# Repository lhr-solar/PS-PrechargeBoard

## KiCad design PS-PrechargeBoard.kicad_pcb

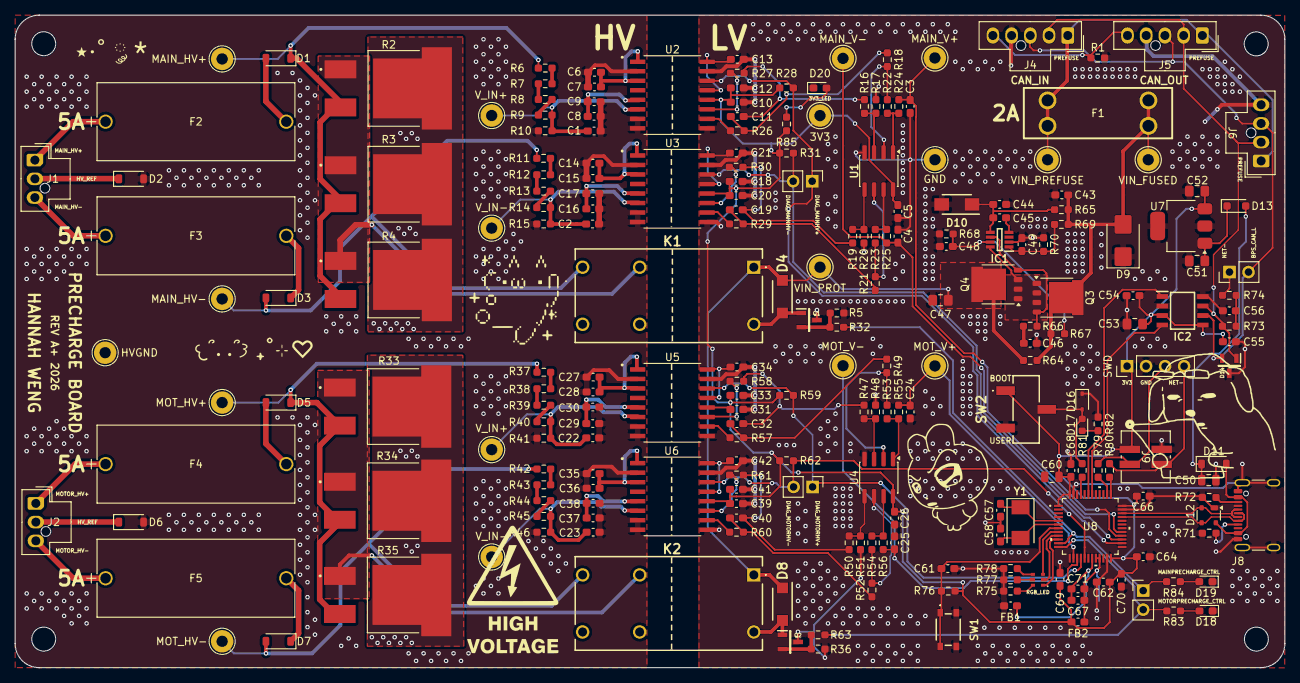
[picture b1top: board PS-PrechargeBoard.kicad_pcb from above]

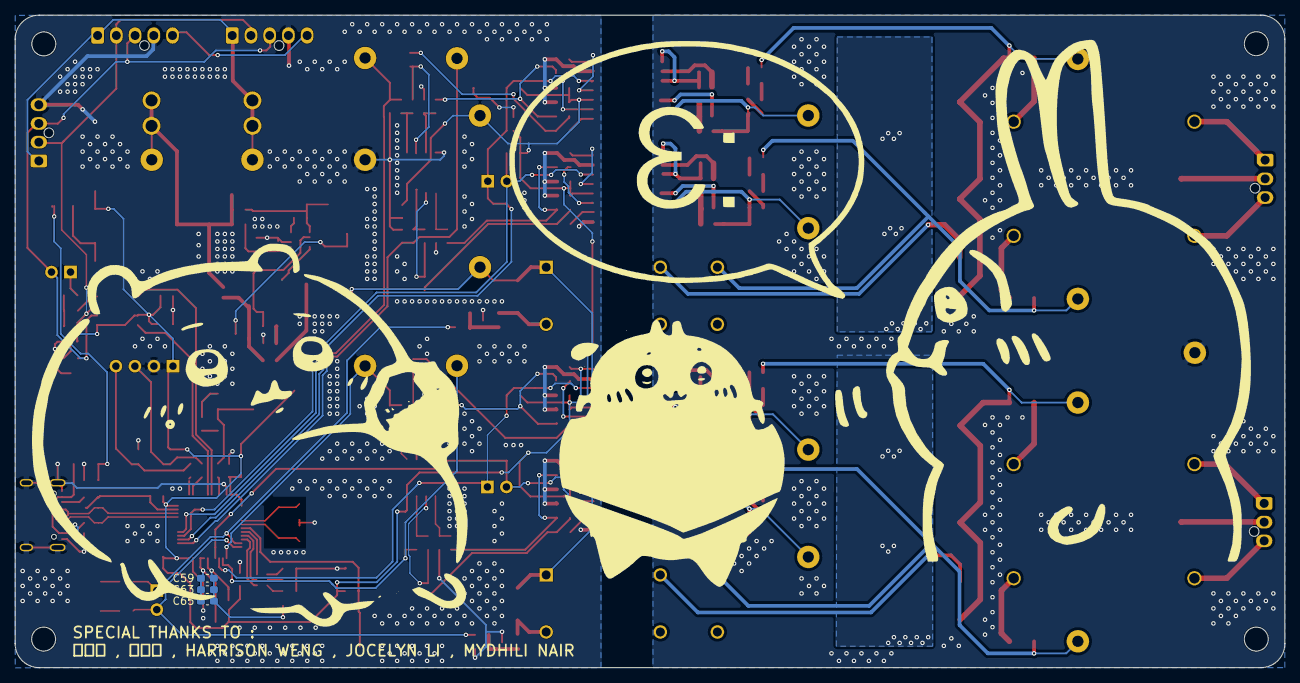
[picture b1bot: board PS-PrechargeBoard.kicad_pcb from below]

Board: 2 copper layers, 169.5 x 87.1 mm, 236 parts (3 on the bottom side), 136 nets.

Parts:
C1, C2, C5, C10, C18, C22, C23, C26, C31, C39, C44, C65, C67: 1u; C_0603_1608Metric_Pad1.08x0.95mm_HandSolder
C3, C4, C11, C19, C24, C25, C32, C40, C46: 10n; C_0603_1608Metric_Pad1.08x0.95mm_HandSolder
C6, C9, C12, C14, C17, C20, C27, C30, C33, C35, C38, C41: 1n; C_0603_1608Metric_Pad1.08x0.95mm_HandSolder
C7, C8, C13, C15, C16, C21, C28, C29, C34, C36, C37, C42, C71: 100n; C_0603_1608Metric_Pad1.08x0.95mm_HandSolder
C43, C48, C49, C54, C55, C56, C59, C61, C62, C63, C64, C66, C68, C69, C70: 0.1u; C_0603_1608Metric_Pad1.08x0.95mm_HandSolder
C45: 220n; C_0603_1608Metric_Pad1.08x0.95mm_HandSolder
C47, C51, C52, C53: 10u; C_0805_2012Metric_Pad1.18x1.45mm_HandSolder
C50, C60: 10u; C_0805_2012Metric
C57, C58: 26p; C_0603_1608Metric_Pad1.08x0.95mm_HandSolder
D1, D2, D3, D5, D6, D7: RSX068MP2STR; D_SOD-123
D4, D8: VSSAF510HM3/H; SODFL5226X100N
D9: SMBJ15CA; D_SMB
D10: SMAF4758A; SODFL5026X125N
D11: D_Schottky; D_SOD-123
D12: SP0503BAHT; SOT-143
D13: SBA130CH-AU_R1_000A1; D_SOD-323_HandSoldering
D14: CDSOT23-T24CAN
D15: RGB_LED
D16: TVS; D_SOD-323
D17: LED; LED_0603_1608Metric
D18, D19, D20: LED; LED_0603_1608Metric_Pad1.05x0.95mm_HandSolder
F1: 2A; Fuse-3557-2
F2, F3, F4, F5: 5A; HV-Fuse
FB1, FB2: FerriteBead; C_0603_1608Metric_Pad1.08x0.95mm_HandSolder
H1, H2, H3, H4: MountingHole; MountingHole_3.2mm_M3
IC1: LM74502DDFR
IC2: TCAN3413DR
J1: HV_Main; Molex_Nano-Fit_105309-xx03_1x03_P2.50mm_Vertical
J2: HV_Motor; Molex_Nano-Fit_105309-xx03_1x03_P2.50mm_Vertical
J3: MOTOR_DIAG; PinHeader_1x02_P2.54mm_Vertical
J4: CAN_IN; Molex_Nano-Fit_105309-xx05_1x05_P2.50mm_Vertical
J5: CAN_OUT; Molex_Nano-Fit_105309-xx05_1x05_P2.50mm_Vertical
J6: DEBUG_NANO; Molex_Nano-Fit_105309-xx04_1x04_P2.50mm_Vertical
J7: PRECHARGE_CTRL; PinHeader_1x02_P2.54mm_Vertical
J8: USB_C_Receptacle_USB2.0_16P; USB_C_Receptacle_GCT_USB4105-xx-A_16P_TopMnt_Horizontal
J9: SWD_Header; SWD_Conn
J10: SWD; PinHeader_1x04_P2.54mm_Vertical
J11: MAIN_DIAG; PinHeader_1x02_P2.54mm_Vertical
JP1: TRM; PinHeader_1x02_P2.54mm_Vertical
K1, K2: DE1a-12V; DE1a12V
Q1, Q2: NMOS; SOT95P237X112-3N
Q3, Q4: PSMN012-100YS; LFPAK56
R1, R64: 0; R_0603_1608Metric_Pad0.98x0.95mm_HandSolder
R2, R3, R4, R33, R34, R35: 50; RES_PWR263S-35-3300F
R5, R10, R15, R16, R17, R18, R19, R20, R21, R22, R23, R36, R41, R46, R47, R48, R49, R50, R51, R52, R53, R54, R65, R76, R81: 10k; R_0603_1608Metric_Pad0.98x0.95mm_HandSolder
R6, R7, R8, R9, R11, R12, R13, R14, R37, R38, R39, R40, R42, R43, R44, R45: 180k; R_0603_1608Metric_Pad0.98x0.95mm_HandSolder
R24, R25, R26, R27, R29, R30, R55, R56, R57, R58, R60, R61: 10; R_0603_1608Metric_Pad0.98x0.95mm_HandSolder
R28, R31, R59, R62: 47k; R_0603_1608Metric_Pad0.98x0.95mm_HandSolder
R32, R63: 100; R_0603_1608Metric_Pad0.98x0.95mm_HandSolder
R66: 33; R_0603_1608Metric_Pad0.98x0.95mm_HandSolder
R67, R69: 100k; R_0603_1608Metric_Pad0.98x0.95mm_HandSolder
R68: 7.32k; R_0603_1608Metric_Pad0.98x0.95mm_HandSolder
R70: 15.8k; R_0603_1608Metric_Pad0.98x0.95mm_HandSolder
R71, R72: 5.1k; R_0603_1608Metric_Pad0.98x0.95mm_HandSolder
R73, R74: 60; R_0603_1608Metric_Pad0.98x0.95mm_HandSolder
R75, R77, R78, R82, R83, R84, R85: 1k; R_0603_1608Metric_Pad0.98x0.95mm_HandSolder
R79, R80: 22; R_0603_1608Metric_Pad0.98x0.95mm_HandSolder
SW1: Reset; TL3365AF180QG
SW2: SW_SPDT; BootSW
TP1: MOT_HV+; TestPoint_THTPad_D3.0mm_Drill1.5mm
TP2: MAIN_HV+; TestPoint_THTPad_D3.0mm_Drill1.5mm
TP3: HVGND; TestPoint_THTPad_D3.0mm_Drill1.5mm
TP4: MAIN_HV-; TestPoint_THTPad_D3.0mm_Drill1.5mm
TP5: MOT_HV-; TestPoint_THTPad_D3.0mm_Drill1.5mm
TP6: 3V3; TestPoint_THTPad_D3.0mm_Drill1.5mm
TP7: VIN_PROT; TestPoint_THTPad_D3.0mm_Drill1.5mm
TP8: VIN_PREFUSE; TestPoint_THTPad_D3.0mm_Drill1.5mm
TP9: MAIN_V+; TestPoint_THTPad_D3.0mm_Drill1.5mm
TP10: MAIN_V-; TestPoint_THTPad_D3.0mm_Drill1.5mm
TP11: GND; TestPoint_THTPad_D3.0mm_Drill1.5mm
TP12: VIN_FUSED; TestPoint_THTPad_D3.0mm_Drill1.5mm
TP13: MOT_V+; TestPoint_THTPad_D3.0mm_Drill1.5mm
TP14: MOT_V-; TestPoint_THTPad_D3.0mm_Drill1.5mm
TP15, TP19: V_IN+; TestPoint_THTPad_D3.0mm_Drill1.5mm
TP16, TP20: V_IN-; TestPoint_THTPad_D3.0mm_Drill1.5mm
U1, U4: TLV9002QDRQ1; SOIC-8_3.9x4.9mm_P1.27mm
U2, U3, U5, U6: SOIC127P1030X265-16N
U7: MCP1826S; SOT-223-3_TabPin2
U8: STM32G473CETx; 48PinMCU
Y1: Crystal; Crystal_SMD_Abracon_ABM3-2Pin_5.0x3.2mm

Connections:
3V3: C5.1, C10.1, C12.1, C18.1, C20.1, C26.1, C31.1, C33.1, C39.1, C41.1, C52.2, C53.1, C54.1, C55.1, C60.1, C62.1, C64.1, C66.1, C68.1, C69.1, C70.1, FB2.1, IC2.3 (VCC), IC2.5 (SHDNV_IO), J9.1, J10.1, R28.1, R31.1, R59.1, R62.1, R76.2, R85.1, SW2.1 (A), TP6.1 (1_1), U1.8 (V+), U2.12 (VDD), U3.12 (VDD), U4.8 (V+), U5.12 (VDD), U6.12 (VDD), U7.3 (VO), U8.1 (VBAT), U8.24 (VDD), U8.36 (VDD), U8.48 (VDD)
/48PinMCU/BOOT0: R81.1, U8.45 (PB8-BOOT0)
/48PinMCU/GNDA: C59.2, C63.2, C65.2, C67.2, C71.2, FB1.1, U8.19 (VSSA)
/48PinMCU/NRST: C61.1, R76.1, SW1.1, U8.7 (PG10-NRST)
/48PinMCU/PA0: D15.5, U8.8 (PA0-GPIO_BLUE)
/48PinMCU/PA1: D15.3, U8.9 (PA1_GPIO_RED)
/48PinMCU/PA2: D15.1, U8.10 (PA2-GPIO_GREEN)
/48PinMCU/SWCLK: R79.1, U8.38 (PA14)
/48PinMCU/SWDIO: R80.1, U8.37 (PA13)
/48PinMCU/VDDA: C59.1, C63.1, C65.1, C67.1, C71.1, FB2.2, U8.20 (VREF+), U8.21 (VDDA)
/BPS_CAN_H: D14.1 (CAN_H), IC2.7 (CANH), J4.2 (CAN_H), J5.2 (CAN_H), J6.2 (CAN_H), R73.1
/BPS_CAN_L: D14.2 (CAN_L), IC2.6 (CANL), J4.3 (CAN_L), J5.3 (CAN_L), J6.3 (CAN_L), JP1.2 (B)
/CAN_RX: IC2.4 (RXD), U8.42 (PB5)
/CAN_TX: IC2.1 (TXD), U8.43 (PB6)
/DIAG_MAINHV+: J11.1, R28.2, U2.14 (DIAG), U8.26 (PB12)
/DIAG_MAINHV-: J11.2, R31.2, U3.14 (DIAG), U8.27 (PB13)
/DIAG_MOTORHV+: J3.1, R59.2, U5.14 (DIAG), U8.16 (PB0)
/DIAG_MOTORHV-: J3.2, R62.2, U6.14 (DIAG), U8.17 (PB1)
/LV Power/PowerProtection/EN/UVLO: C49.1, IC1.1 (EN/UVLO), R69.2, R70.2
/LV Power/PowerProtection/OV: C48.1, IC1.7 (OV), R67.2, R68.1
/LV Power/PowerProtection/gate: IC1.6 (GATE), Q3.4, Q4.4, R66.2
/LV Power/PowerProtection/source: IC1.8 (SRC), Q3.1, Q3.2, Q3.3, Q4.1, Q4.2, Q4.3
/LV Power/USB-C_Connector/CC1: J8.A5 (CC1), R71.2
/LV Power/USB-C_Connector/CC2: J8.B5 (CC2), R72.2
/LV Power/USB-C_Connector/VBUS_IN: D11.2 (A), D12.4 (K), J8.A4 (VBUS), J8.A9 (VBUS), J8.B4 (VBUS), J8.B9 (VBUS)
/LV Power/USB_5V: C50.2, D11.1 (K), D13.2 (A)
/MAINPRECHARGE_CTRL: J7.1, R32.1, R84.1, U8.11 (PA3)
/MAIN_RES_HV-: K1.3 (COM), R2.1, R3.1, R4.1
/MAIN_V+: C3.1, R24.2, TP9.1 (1_1), U8.28 (PB14)
/MAIN_V-: C4.1, R25.2, TP10.1 (1_1), U8.29 (PB15)
/MOTPRECHARGE_CTRL: J7.2, R63.1, R83.1, U8.12 (PA4)
/MOT_RES_HV-: K2.3 (COM), R33.1, R34.1, R35.1
/MOT_V+: C24.1, R55.2, TP13.1 (1_1), U8.14 (PA6)
/MOT_V-: C25.1, R56.2, TP14.1 (1_1), U8.15 (PA7)
/Main_Fuse/HV_PREFUSE+: F2.1, J1.1
/Main_Fuse/HV_PREFUSE-: F3.1, J1.3
/Main_Fuse/HV_REF: D2.1 (K), J1.2
/Main_Fuse/RESISTOR: R2.3, R3.3, R4.3
/Main_Precharge/DRAIN: D4.2 (A), K1.8 (COIL-), Q1.1 (D)
/Main_VoltageSensor/OUTN_HV+: C11.1, R18.1, R26.2
/Main_VoltageSensor/OUTN_HV-: C19.1, R21.1, R29.2
/Main_VoltageSensor/OUTP_HV+: C11.2, R16.1, R27.2
/Main_VoltageSensor/OUTP_HV-: C19.2, R19.1, R30.2
/Main_VoltageSensor/V_IN+: C1.1, R9.2, R10.1, TP15.1 (1_1), U2.6 (IN)
/Main_VoltageSensor/V_IN-: C2.1, R14.2, R15.1, TP16.1 (1_1), U3.6 (IN)
/Main_VoltageSensor/VoltageSensor_HV+/3V3_DCDC: C13.2, U2.13 (LDO_OUT), U2.16 (DCDC_IN)
/Main_VoltageSensor/VoltageSensor_HV+/HLDO_OUT: C8.2, C9.2, U2.5 (HLDO_OUT)
/Main_VoltageSensor/VoltageSensor_HV+/HV_DCDC: C6.1, C7.2, U2.1 (DCDC_OUT), U2.3 (HLDO_IN)
/Main_VoltageSensor/VoltageSensor_HV+/OUTN: R26.1, U2.10 (OUTN)
/Main_VoltageSensor/VoltageSensor_HV+/OUTP: R27.1, U2.11 (OUTP)
/Main_VoltageSensor/VoltageSensor_HV-/3V3_DCDC: C21.2, U3.13 (LDO_OUT), U3.16 (DCDC_IN)
/Main_VoltageSensor/VoltageSensor_HV-/HLDO_OUT: C16.2, C17.2, U3.5 (HLDO_OUT)
/Main_VoltageSensor/VoltageSensor_HV-/HV_DCDC: C14.1, C15.2, U3.1 (DCDC_OUT), U3.3 (HLDO_IN)
/Main_VoltageSensor/VoltageSensor_HV-/OUTN: R29.1, U3.10 (OUTN)
/Main_VoltageSensor/VoltageSensor_HV-/OUTP: R30.1, U3.11 (OUTP)
/Motor_Fuse/HV_PREFUSE+: F4.1, J2.1
/Motor_Fuse/HV_PREFUSE-: F5.1, J2.3
/Motor_Fuse/HV_REF: D6.1 (K), J2.2
/Motor_Fuse/RESISTOR: R33.3, R34.3, R35.3
/Motor_Precharge/DRAIN: D8.2 (A), K2.8 (COIL-), Q2.1 (D)
/Motor_VoltageSensor/OUTN_HV+: C32.1, R49.1, R57.2
/Motor_VoltageSensor/OUTN_HV-: C40.1, R52.1, R60.2
/Motor_VoltageSensor/OUTP_HV+: C32.2, R47.1, R58.2
/Motor_VoltageSensor/OUTP_HV-: C40.2, R50.1, R61.2
/Motor_VoltageSensor/V_IN+: C22.1, R40.2, R41.1, TP19.1 (1_1), U5.6 (IN)
/Motor_VoltageSensor/V_IN-: C23.1, R45.2, R46.1, TP20.1 (1_1), U6.6 (IN)
/Motor_VoltageSensor/VoltageSensor_HV+/3V3_DCDC: C34.2, U5.13 (LDO_OUT), U5.16 (DCDC_IN)
/Motor_VoltageSensor/VoltageSensor_HV+/HLDO_OUT: C29.2, C30.2, U5.5 (HLDO_OUT)
/Motor_VoltageSensor/VoltageSensor_HV+/HV_DCDC: C27.1, C28.2, U5.1 (DCDC_OUT), U5.3 (HLDO_IN)
/Motor_VoltageSensor/VoltageSensor_HV+/OUTN: R57.1, U5.10 (OUTN)
/Motor_VoltageSensor/VoltageSensor_HV+/OUTP: R58.1, U5.11 (OUTP)
/Motor_VoltageSensor/VoltageSensor_HV-/3V3_DCDC: C42.2, U6.13 (LDO_OUT), U6.16 (DCDC_IN)
/Motor_VoltageSensor/VoltageSensor_HV-/HLDO_OUT: C37.2, C38.2, U6.5 (HLDO_OUT)
/Motor_VoltageSensor/VoltageSensor_HV-/HV_DCDC: C35.1, C36.2, U6.1 (DCDC_OUT), U6.3 (HLDO_IN)
/Motor_VoltageSensor/VoltageSensor_HV-/OUTN: R60.1, U6.10 (OUTN)
/Motor_VoltageSensor/VoltageSensor_HV-/OUTP: R61.1, U6.11 (OUTP)
/SHIELD: J4.5 (SHIELD), J5.5 (SHIELD), R1.1
/USB_D+: D12.2 (K), J8.A6 (D+), J8.B6 (D+), U8.34 (PA12)
/USB_D-: D12.3 (K), J8.A7 (D-), J8.B7 (D-), U8.33 (PA11)
/VIN_FUSED: C43.1, D9.2 (A2), F1.1, Q3.5, R64.1, R65.2, R67.1, R69.1, TP12.1 (1_1)
/VIN_PREFUSE: F1.2, J4.1 (12V), J5.1 (12V), J6.1 (12V), TP8.1 (1_1)
/VIN_PROT: C47.1, D4.1 (K), D8.1 (K), K1.1 (COIL+), K2.1 (COIL+), Q4.5, R64.2, TP7.1 (1_1)
GND: C3.2, C4.2, C5.2, C10.2, C12.2, C13.1, C18.2, C20.2, C21.1, C24.2, C25.2, C26.2, C31.2, C33.2, C34.1, C39.2, C41.2, C42.1, C43.2, C44.1, C46.2, C47.2, C48.2, C49.2, C50.1, C51.1, C52.1, C53.2, C54.2, C55.2, C56.1, C57.1, C58.2, C60.2, C61.2, C62.2, C64.2, C66.2, C68.2, C69.2, C70.2, D9.1 (A1), D10.2 (A), D12.1 (A), D14.3 (GND), D16.1 (A1), D18.1 (K), D19.1 (K), D20.1 (K), FB1.2, IC1.2 (GND), IC2.2 (GND), IC2.8 (STB), J4.4 (GND), J5.4 (GND), J6.4 (GND), J8.A1 (GND), J8.A12 (GND), J8.B1 (GND), J8.B12 (GND), J8.S1 (SHIELD), J8.S2 (Shield), J8.S3 (Shield), J8.S4 (Shield), J9.2, J10.2, Q1.3 (S), Q2.3 (S), R1.2, R5.1, R17.2, R20.2, R36.1, R48.2, R51.2, R68.2, R70.1, R71.1, R72.1, R75.2, R77.2, R78.2, R82.2, SW1.2, SW2.3 (C), TP11.1 (1_1), U1.4 (V-), U2.9 (GND), U2.15 (DCDC_GND), U3.9 (GND), U3.15 (DCDC_GND), U4.4 (V-), U5.9 (GND), U5.15 (DCDC_GND), U6.9 (GND), U6.15 (DCDC_GND), U7.2 (GND), U8.23 (VSS), U8.35 (VSS), U8.47 (VSS)
HVGND: C1.2, C2.2, C6.2, C7.1, C8.1, C9.1, C14.2, C15.1, C16.1, C17.1, C22.2, C23.2, C27.2, C28.1, C29.1, C30.1, C35.2, C36.1, C37.1, C38.1, D2.2 (A), D6.2 (A), R10.2, R15.2, R41.2, R46.2, TP3.1 (1_1), U2.2 (DCDC_HGND), U2.7 (HGND), U2.8 (HGND), U3.2 (DCDC_HGND), U3.7 (HGND), U3.8 (HGND), U5.2 (DCDC_HGND), U5.7 (HGND), U5.8 (HGND), U6.2 (DCDC_HGND), U6.7 (HGND), U6.8 (HGND)
MAIN_HV+: D1.1 (K), R2.2, R3.2, R4.2, R6.1, TP2.1 (1_1)
MAIN_HV-: D3.2 (A), K1.4 (N.O.), R11.1, TP4.1 (1_1)
MOT_HV+: D5.1 (K), R33.2, R34.2, R35.2, R37.1, TP1.1 (1_1)
MOT_HV-: D7.2 (A), K2.4 (N.O.), R42.1, TP5.1 (1_1)
unnamed: C46.1, R66.1
unnamed: C56.2, R73.2, R74.1
unnamed: D1.2 (A), F2.2
unnamed: D3.1 (K), F3.2
unnamed: D5.2 (A), F4.2
unnamed: D7.1 (K), F5.2
unnamed: C44.2, C45.1, D10.1 (K), IC1.5 (VS), R65.1
unnamed: C51.2, D13.1 (K), U7.1 (VI)
unnamed: D15.2, R75.1
unnamed: D15.4, R77.1
unnamed: D15.6, R78.1
unnamed: D16.2 (A2), D17.2 (A), R81.2, SW2.2 (B)
unnamed: D17.1 (K), R82.1
unnamed: D18.2 (A), R83.2
unnamed: D19.2 (A), R84.2
unnamed: D20.2 (A), R85.2
unnamed: C45.2, IC1.4 (VCAP)
unnamed: J9.3, J10.3, R79.2
unnamed: J9.4, J10.4, R80.2
unnamed: JP1.1 (A), R74.2
unnamed: Q1.2 (G), R5.2, R32.2
unnamed: Q2.2 (G), R36.2, R63.2
unnamed: R6.2, R7.1
unnamed: R7.2, R8.1
unnamed: R8.2, R9.1
unnamed: R11.2, R12.1
unnamed: R12.2, R13.1
unnamed: R13.2, R14.1
unnamed: R22.2, R24.1, U1.1
unnamed: R23.2, R25.1, U1.7
unnamed: R37.2, R38.1
unnamed: R38.2, R39.1
unnamed: R39.2, R40.1
unnamed: R42.2, R43.1
unnamed: R43.2, R44.1
unnamed: R44.2, R45.1
unnamed: R53.2, R55.1, U4.1
unnamed: R54.2, R56.1, U4.7
unnamed: R16.2, R17.1, U1.3 (+)
unnamed: R18.2, R22.1, U1.2 (-)
unnamed: R19.2, R20.1, U1.5 (+)
unnamed: R21.2, R23.1, U1.6 (-)
unnamed: R47.2, R48.1, U4.3 (+)
unnamed: R49.2, R53.1, U4.2 (-)
unnamed: R50.2, R51.1, U4.5 (+)
unnamed: R52.2, R54.1, U4.6 (-)
unnamed: C57.2, U8.5 (PF0-OSC_IN), Y1.1
unnamed: C58.1, U8.6 (PF1-OSC_OUT), Y1.2

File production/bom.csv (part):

Reference,Value,Exclude from BOM,Footprint,Datasheet,LCSC P/N,Mouser P/N,P/N,Description
Y1,Crystal,,LHRS_Passives:Crystal_SMD_Abracon_ABM3-2Pin_5.0x3.2mm,kicad-embed://HSE_Crystal.pdf,C144380,815-ABM3-8-D2Y-T,ABM3-8.000MHZ-D2Y-T,Two pin crystal
U8,STM32G473CETx,,LHRS_Special:48PinMCU,kicad-embed://stm32g473cb.pdf,C730113,511-STM32G473CET6,STM32G473CET6,"STMicroelectronics Arm Cortex-M4 MCU, 128-512KB flash, 128KB RAM, 170 MHz, 1.71-3.6V, 38 GPIO, LQFP48"
U7,MCP1826S,,Package_TO_SOT_SMD:SOT-223-3_TabPin2,http://ww1.microchip.com/downloads/en/DeviceDoc/22057B.pdf,C126055,579-MCP1826S-3302EDB,MCP1826S-3302E/DB,"1000mA, Low-Voltage, Low Quiescent Current LDO Regulator, SOT-223, TO-220, TO-263"
"U2,U3,U5,U6",,,Precharge_Board:SOIC127P1030X265-16N,https://www.ti.com/lit/ds/symlink/amc3311-q1.pdf?ts=1793258758946,,595-AMC3311QDWERQ1,AMC3311QDWERQ1,
"U1,U4",TLV9002QDRQ1,,Package_SO:SOIC-8_3.9x4.9mm_P1.27mm,kicad-embed://tlv9002-q1.pdf,,595-TLV9002QDRQ1,TLV9002QDRQ1,
SW2,SW_SPDT,,LHRS_Special:BootSW,kicad-embed://BootSW.pdf,-,710-450406020024,4.50406E+11,"Switch, single pole double throw"
SW1,Reset,,LHRS_Special:TL3365AF180QG,kicad-embed://ResetBtn.pdf,C2886926,612-TL3365AF180QG,TL3365AF180QG,"Push button switch, generic, two pins"
"R79,R80",22,,Resistor_SMD:R_0603_1608Metric_Pad0.98x0.95mm_HandSolder,,C2930077,279-CRG0603F22R,CRG0603F22R,Resistor
"R75,R77,R78,R82,R83,R84,R85",1k,,Resistor_SMD:R_0603_1608Metric_Pad0.98x0.95mm_HandSolder,,C21190,71-CRCW0603-1.0K-E3,CRCW06031K00FKEI ,Resistor
"R73,R74",60,,Resistor_SMD:R_0603_1608Metric_Pad0.98x0.95mm_HandSolder,,C166918,71-CRCW0603-60.4-E3,CRCW060360R4FKEA,Resistor
"R71,R72",5.1k,,Resistor_SMD:R_0603_1608Metric_Pad0.98x0.95mm_HandSolder,,C23186,303-0603WAF5101T5E,0603WAF5101T5E,Resistor
R70,15.8k,,Resistor_SMD:R_0603_1608Metric_Pad0.98x0.95mm_HandSolder,,C843918,71-CRCW0603-15.8K-E3,CRCW060315K8FKEA,"Resistor, US symbol"
R68,7.32k,,Resistor_SMD:R_0603_1608Metric_Pad0.98x0.95mm_HandSolder,,C862286,603-RT0603BRD077K32L,RT0603BRE077K32L,"Resistor, US symbol"
"R67,R69",100k,,Resistor_SMD:R_0603_1608Metric_Pad0.98x0.95mm_HandSolder,,C25803,303-0603WAF1003T5E,0603WAF1003T5E,"Resistor, US symbol"
R66,33,,Resistor_SMD:R_0603_1608Metric_Pad0.98x0.95mm_HandSolder,,C2074308,594-MCT06030C3309FP5,MCT06030C3309FP500,"Resistor, US symbol"
"R32,R63",100,,Resistor_SMD:R_0603_1608Metric_Pad0.98x0.95mm_HandSolder,,,303-0603WAF1000T5E,0603WAF1000T5E,Resistor
"R28,R31,R59,R62",47k,,Resistor_SMD:R_0603_1608Metric_Pad0.98x0.95mm_HandSolder,,,71-CRCW060347K0FKECC,CRCW060347K0FKECC,Resistor
"R24,R25,R26,R27,R29,R30,R55,R56,R57,R58,R60,R61",10,,Resistor_SMD:R_0603_1608Metric_Pad0.98x0.95mm_HandSolder,,,71-CRCW0603-10K-E3,CRCW060310R0FKEE,Resistor
"R6,R7,R8,R9,R11,R12,R13,R14,R37,R38,R39,R40,R42,R43,R44,R45",180k,,Resistor_SMD:R_0603_1608Metric_Pad0.98x0.95mm_HandSolder,,,791-RMC16K184FTP,RMC16K184FTP,Resistor
"R5,R10,R15,R16,R17,R18,R19,R20,R21,R22,R23,R36,R41,R46,R47,R48,R49,R50,R51,R52,R53,R54,R65,R76,R81",10k,,Resistor_SMD:R_0603_1608Metric_Pad0.98x0.95mm_HandSolder,,C20443035,303-0603WAF1002T5E,0603WAF1002T5E,Precharge Resistor
"R2,R3,R4,R33,R34,R35",50,,Precharge_Board:RES_PWR263S-35-3300F,kicad-embed://pwr263s-35.pdf,,652-PWR263S353300F,PWR263S-35-3300F,Precharge Resistor
"R1,R64",0,,Resistor_SMD:R_0603_1608Metric_Pad0.98x0.95mm_HandSolder,,,71-CRCW06030000Z0EI,CRCW06030000Z0EE,Resistor
"Q3,Q4",PSMN012-100YS,,Package_TO_SOT_SMD:LFPAK56,kicad-embed://PSMN012-100YS.pdf,C20443035,771-PSMN012-100YSFX,PSMN012-100YSFX,"N-MOSFET transistor, drain/source/gate"
"Q1,Q2",NMOS,,Precharge_Board:SOT95P237X112-3N,https://ngspice.sourceforge.io/docs/ngspice-html-manual/manu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,,942-IRLML0030TRPBF,IRLML0030TRPBF,"N-MOSFET transistor, drain/source/gate"
"K1,K2",DE1a-12V,,Precharge_Board:DE1a12V,https://www.mouser.it/datasheet/2/315/mech_eng_de-1299471.pdf,,769-DE1A-12V,DE1a-12V,"General Purpose Relay SPST-NO (1 Form A) 12VDC Coil Through Hole , 16.7mA , 720 Ohms , -40C ~ 70C"
J9,SWD_Header,,LHRS_Connectors:SWD_Conn,kicad-embed://Conn_02x02_Odd_Even.pdf,C17492485,538-87832-0406,878320406,"Generic connector, double row, 02x02"
J8,USB_C_Receptacle_USB2.0_16P,,LHRS_Connectors:USB_C_Receptacle_GCT_USB4105-xx-A_16P_TopMnt_Horizontal,https://www.usb.org/sites/default/files/documents/usb_type-c.zip,C3020560,640-USB4105-GF-A,USB4105-GF-A,USB 2.0-only 16P Type-C Receptacle connector
J7,PRECHARGE_CTRL,,Connector_PinHeader_2.54mm:PinHeader_1x02_P2.54mm_Vertical,,,,,"Generic connector, single row, 01x02, script generated"
J6,DEBUG_NANO,,LHRS_Connectors:Molex_Nano-Fit_105309-xx04_1x04_P2.50mm_Vertical,,,538-105309-1104,1053091104,
J5,CAN_OUT,,LHRS_Connectors:Molex_Nano-Fit_105309-xx05_1x05_P2.50mm_Vertical,,,538-105309-1105,1053091105,
J4,CAN_IN,,LHRS_Connectors:Molex_Nano-Fit_105309-xx05_1x05_P2.50mm_Vertical,,,538-105309-1105,1053091105,
J2,HV_Motor,,LHRS_Connectors:Molex_Nano-Fit_105309-xx03_1x03_P2.50mm_Vertical,,,538-105309-1203,105309-1203,"Generic connector, single row, 01x03, script generated (kicad-library-utils/schlib/autogen/connector/)"
J1,HV_Main,,LHRS_Connectors:Molex_Nano-Fit_105309-xx03_1x03_P2.50mm_Vertical,,,538-105309-1203,105309-1203,"Generic connector, single row, 01x03, script generated (kicad-library-utils/schlib/autogen/connector/)"
IC2,TCAN3413DR,,LHRS_Passives:TCAN3413DR,kicad-embed://tcan3413.pdf,C22433320,595-TCAN3413DR,TCAN3413DR,1/1 Transceiver Half CANbus 8-SOIC
IC1,LM74502DDFR,,LHRS_Power:LM74502DDFR,kicad-embed://LM74502DDFR.pdf,C3236215,595-LM74502DDFR,LM74502DDFR,"Hot Swap Voltage Controllers 3.2-V to 65-V industrial RPP controller with load disconnect, OVP, and high gate drive"
"FB1,FB2",FerriteBead,,Capacitor_SMD:C_0603_1608Metric_Pad1.08x0.95mm_HandSolder,kicad-embed://FerriteBead.pdf,C354394,81-BLM18PG121SH1D,BLM18PG121SH1D,Ferrite bead
"F2,F3,F4,F5",5A,,LHRS_Power:HV-Fuse,,,576-05200101Z,05200101Z ,Fuse
F1,2A,,LHRS_Power:Fuse-3557-2,kicad-embed://3557-2-datasheet.pdf,C3205238,534-3557-2,3557-2,"Fuse, low-profile"
"D17,D18,D19,D20",LED,,LED_SMD:LED_0603_1608Metric_Pad1.05x0.95mm_HandSolder,kicad-embed://Blue LED.pdf,C125103,327-FR1101C2005MTR,FR1101C-2005-M-TR,Light emitting diode
D16,TVS,,Diode_SMD:D_SOD-323,kicad-embed://TVS.pdf,C725495,771-PESD15VL1BA-T/R,PESD15VL1BA,Bidirectional transient-voltage-suppression diode
D15,RGB_LED,,LHRS_Special:RGB_LED,kicad-embed://EVER-S-A0007433884-1.pdf,C264519,638-19337R6GHBHCA01T,19-337/R6GHBHC-A01/2T ,
D14,CDSOT23-T24CAN,,LHRS_Passives:CDSOT23-T24CAN,kicad-embed://cdsot23-t24can.pdf,C2959841,652-CDSOT23-T24CAN,CDSOT23-T24CAN,"Bourns CDSOT23-T24CAN, Dual Bi-Directional ESD Protection Diode, 3-Pin SOT-23"
D13,SBA130CH-AU_R1_000A1,,Diode_SMD:D_SOD-323_HandSoldering,https://www.mouser.com/datasheet/3/3736/1/11145663EF9055F8C1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,C191023,241-SBA130CH-AUR10A1,SBA130CH-AU_R1_000A1 ,"Schottky diode, small symbol"
D12,SP0503BAHT,,Package_TO_SOT_SMD:SOT-143,kicad-embed://Littelfuse-TVS-Diode-Array-SP05-Datasheet.pdf,C7074,576-SP0503BAHTG,SP0503BAHTG,
D11,D_Schottky,,Diode_SMD:D_SOD-123,,C82544,621-BAT760-7,BAT760-7,Schottky diode
D10,SMAF4758A,,LHRS_Passives:SODFL5026X125N,kicad-embed://SMAF4758A.pdf,C183490,833-SMAF4758A-TP,SMAF4758A,Zener diode
D9,SMBJ15CA,,Diode_SMD:D_SMB,kicad-embed://SMBJ15CA.pdf,C669039,78-SMBJ15CA,SMBJ15CA,TVS diode
"D4,D8",VSSAF510HM3/H,,LHRS_Passives:SODFL5226X100N,kicad-embed://DIOD-S-A0007810469-1.pdf,,621-1N5819HW-F,1N5819HW-7-F,"Diodes Inc B540C-13-F, SMT Schottky Diode, 40V 5A, 2-Pin DO-214AB"
"D1,D2,D3,D5,D6,D7",RSX068MP2STR,,Diode_SMD:D_SOD-123,https://fscdn.rohm.com/en/products/databook/datasheet/discre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,,755-RSX068MP2STR,RSX068MP2STR,Schottky diode
"C57,C58",26p,,Capacitor_SMD:C_0603_1608Metric_Pad1.08x0.95mm_HandSolder,,C92670,791-0603N270F500CT,0603N270F500CT ,Unpolarized capacitor
"C47,C50,C51,C52,C53,C60",10u,,Capacitor_SMD:C_0805_2012Metric_Pad1.18x1.45mm_HandSolder,,C440198,GRM21BR61H106KE43K,GRM21BR61H106KE43K,Unpolarized capacitor
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
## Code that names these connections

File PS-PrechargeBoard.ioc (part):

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Mcu.Name=STM32G473C(B-C-E)Tx
Mcu.Package=LQFP48
Mcu.UserName=STM32G473CETx
PA11.Mode=Device
PA11.Signal=USB_DM
PA12.Mode=Device
PA12.Signal=USB_DP
PA3.Signal=GPIO_Output
PA4.Signal=GPIO_Output
PA6.Mode=IN3-Differential
PA6.Signal=ADC2_IN3
PA7.Mode=IN3-Differential
PA7.Signal=ADC2_IN4
PB0.Signal=GPIO_Input
PB1.Signal=GPIO_Input
PB12.Signal=GPIO_Input
PB13.Signal=GPIO_Input
PB14.Mode=IN4-Differential
PB14.Signal=ADC4_IN4
PB15.Mode=IN4-Differential
PB15.Signal=ADC4_IN5
PB5.Mode=FDCAN_Activate
PB5.Signal=FDCAN2_RX
PB6.Mode=FDCAN_Activate
PB6.Signal=FDCAN2_TX
PF0-OSC_IN.Mode=HSE-External-Oscillator
PF0-OSC_IN.Signal=RCC_OSC_IN
PF1-OSC_OUT.Mode=HSE-External-Oscillator
PF1-OSC_OUT.Signal=RCC_OSC_OUT
RCC.HSE_VALUE=8000000
RCC.SYSCLKFreq_VALUE=16000000
board=custom
